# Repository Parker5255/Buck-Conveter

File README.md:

# Buck-Conveter
KiCad files for the Buck Converter (Power Electronics)

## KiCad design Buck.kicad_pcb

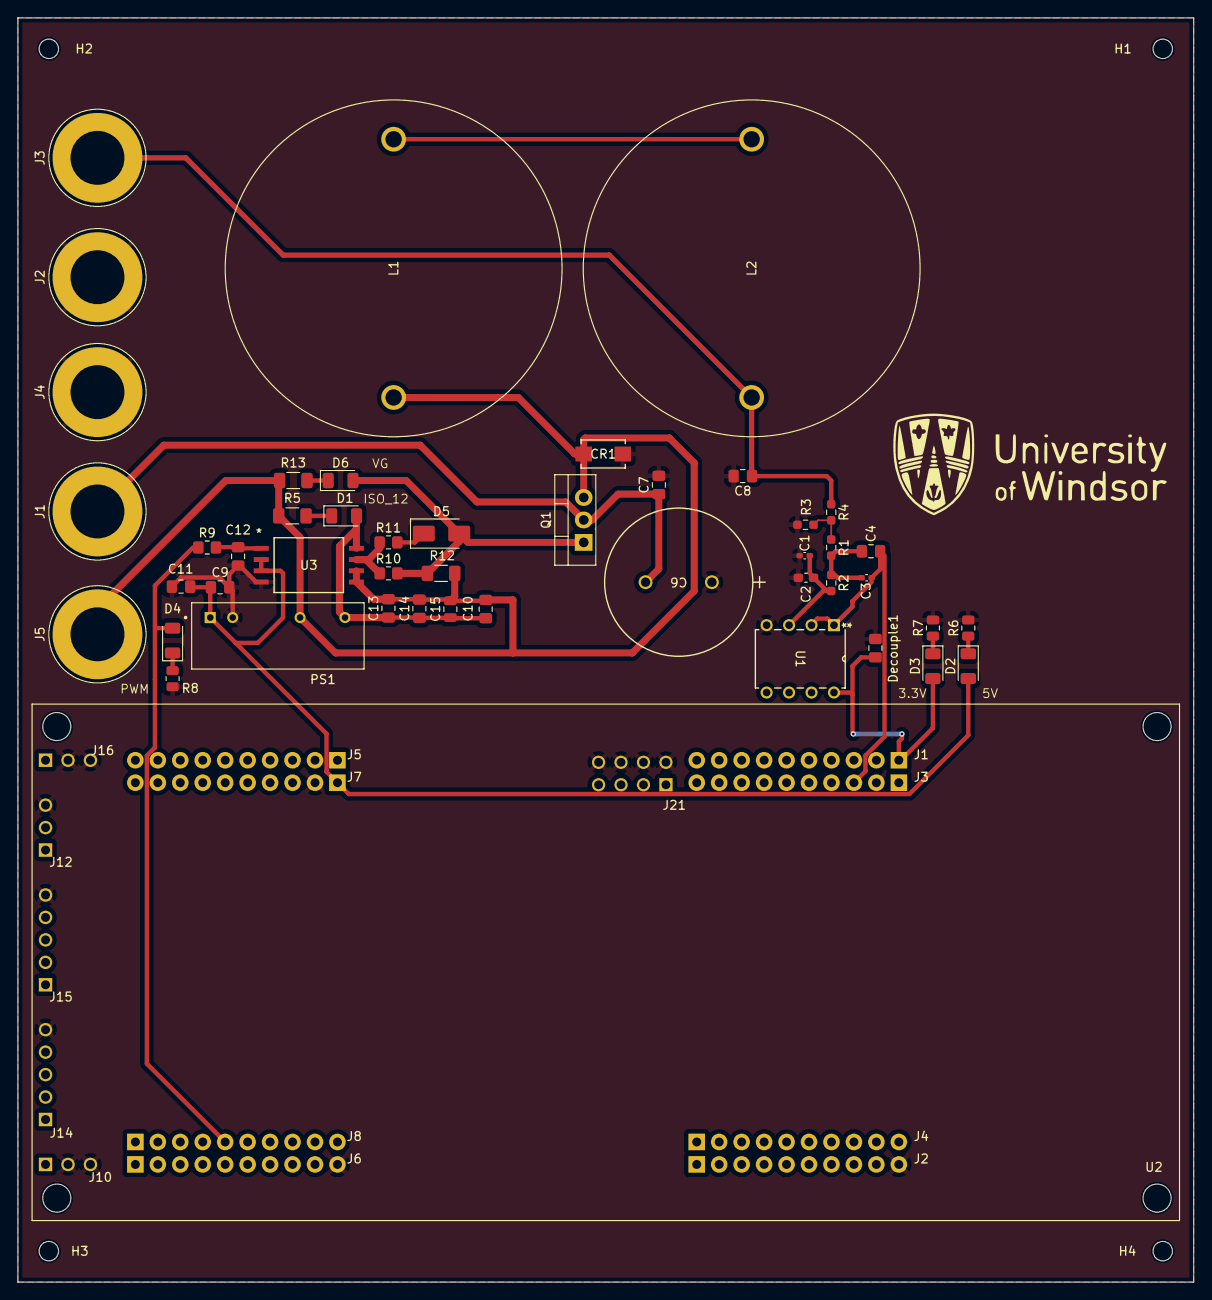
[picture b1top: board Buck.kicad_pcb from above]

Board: 2 copper layers, 133.0 x 143.0 mm, 51 parts (0 on the bottom side), 22 nets.

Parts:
C1: 1.5nF; C_0402_1005Metric_Pad0.74x0.62mm_HandSolder
C2: 5.1nF; C_0603_1608Metric_Pad1.08x0.95mm_HandSolder
C3: 0.62nF; C_0402_1005Metric_Pad0.74x0.62mm_HandSolder
C4: 8.2nF; C_0805_2012Metric_Pad1.18x1.45mm_HandSolder
C6: 47uF; CAP_YX_16X31P5_RUB
C7: 1uF; C_0805_2012Metric_Pad1.18x1.45mm_HandSolder
C8: 2.2uF; C_0805_2012Metric_Pad1.18x1.45mm_HandSolder
C9, C10, C11: 0.1uF; C_0805_2012Metric_Pad1.18x1.45mm_HandSolder
C12: 47 pF; C_0805_2012Metric_Pad1.18x1.45mm_HandSolder
C13: 10uF; C_0805_2012Metric_Pad1.18x1.45mm_HandSolder
C14: 220nF; C_0805_2012Metric_Pad1.18x1.45mm_HandSolder
C15: 10uF; C_0805_2012Metric
CR1: SK510A-LTP; SMADO-214AC_LEAD-FRAME_MCC
D1, D6: IR26-21C_L110_TR8; LED_1206_3216Metric
D2, D3, D4: LED_1206_3216Metric
D5: US2AA; D_SMA
Decouple1: 0.1uF; C_0805_2012Metric_Pad1.18x1.45mm_HandSolder
H1, H2, H3, H4: MountingHole; MountingHole_2.2mm_M2
J1, J2, J3, J4, J5: Conn_01x01_Pin; Banana_Jack_1Pin
L1, L2: 10mH; INDRD2921W163D3810H2616P
PS1: TMV_0512SHI; CONV_TMV_0512SHI
Q1: IRF540N; TO-220-3_Vertical
R1, R2: 10KOhm; R_0603_1608Metric_Pad0.98x0.95mm_HandSolder
R3: 1KOhm; R_0603_1608Metric_Pad0.98x0.95mm_HandSolder
R4: 29.4KOhm; R_0603_1608Metric_Pad0.98x0.95mm_HandSolder
R5, R13: 3.3KOhm; R_1206_3216Metric_Pad1.30x1.75mm_HandSolder
R6, R7, R8: 3.3KOhm; R_0805_2012Metric
R9: 51 Ohm; R_0805_2012Metric_Pad1.20x1.40mm_HandSolder
R10: 7 Ohm; R_0805_2012Metric_Pad1.20x1.40mm_HandSolder
R11: 12 Ohm; R_0805_2012Metric_Pad1.20x1.40mm_HandSolder
R12: 50 Ohm; R_1206_3216Metric_Pad1.30x1.75mm_HandSolder
U1: LM358; P8
U2: LAUNCHXL-F28379D; MOD_LAUNCHXL-F28379D
U3: UCC5304DWVR; SOIC8_DWV_TEX

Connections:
+3.3V: D3.2 (A), Decouple1.1, U1.8 (V+), U2.J1_1 (3.3V_J1)
+5V: C9.1, C11.1, D2.2 (A), PS1.1 (+VIN_(VCC)), U2.J7_1 (+5V_J7), U3.2 (VCCI), U3.3 (VCCI)
/GD/GD_PWM: R10.1, R11.1, U3.7 (OUT)
/GD/ISO_12: C10.1, C13.1, C14.1, C15.1, D1.2 (A), PS1.7 (+VOUT), U3.8 (VDD)
/GD/PWM_FILT: C12.1, R9.2, U3.1 (IN)
/PWM: D4.2 (A), R9.1, U2.J8_5 (GPIO11/PWMOUT6B)
/PowerStage/Vin: C6.2, C7.1, J1.1, Q1.2 (D)
/VFILT: C3.2, C4.2, U1.1, U1.2 (-), U2.J3_3 (ADCIN14/ANALOGIN)
/VG: D5.2 (A), D6.2 (A), Q1.1 (G), R10.2, R12.1
/VOUT: C8.1, J3.1, L2.2, R4.1
/VSW: C10.2, C13.2, C14.2, C15.2, CR1.1, J5.1, L1.1, PS1.5 (-VOUT), Q1.3 (S), R5.2, R12.2, R13.2, U3.5 (VSS), U3.6 (VSS)
GND: C1.2, C2.2, C6.1, C7.2, C8.2, C9.2, C11.2, C12.2, CR1.2, Decouple1.2, J2.1, J4.1, PS1.2 (-VIN_(GND)), R3.1, R6.2, R7.2, R8.2, U1.4 (V-), U2.J2_10 (GND_J2), U2.J3_2 (GND_J3), U2.J6_10 (GND_J6), U2.J7_2 (GND_J7), U2.J10_2 (GND_J10), U2.J10_3 (GND_J10__1), U2.J12_3 (GND_J12), U2.J14_5 (GND_J14), U2.J15_5 (GND_J15), U2.J16_2 (GND_J16), U2.J16_3 (GND_J16__1), U2.J21_2 (TP21/GND), U2.J21_4 (TP22/GND), U2.J21_6 (TP23/GND), U2.J21_8 (TP24/GND), U3.4 (GND)
unnamed: C3.1, C4.1, R1.2, R2.1
unnamed: D1.1 (K), R5.1
unnamed: D2.1 (K), R6.1
unnamed: D3.1 (K), R7.1
unnamed: D4.1 (K), R8.1
unnamed: D5.1 (K), R11.2
unnamed: D6.1 (K), R13.1
unnamed: L1.2, L2.1
unnamed: R1.1, R3.2, R4.2
unnamed: C1.1, C2.1, R2.2, U1.3 (+)

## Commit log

2025-02-25 Add files via upload
    Main files of the KiCAD Buck Converter Project
2025-03-04 Add files via upload
    Most Recent PCB. Has 0.5 mm Traces, through hole op amp, and mounting holes.
